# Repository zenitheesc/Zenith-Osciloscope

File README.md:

<h1 align="center" style="color:white; background-color:black">Zenith Osciloscope</h1>
<h4 align="center">This project is an educational oscilloscope based on STM32F103C8T6 aimed to be used by students on PC laboratories. The oscilloscope get some samples in a small frequency limited by the range in the STM AD converter. This samples was stored in a data pack on STM and passed by serial communication to PC. In the PC, a interface software read the serial and plot the data package</h4>

<p align="center">

</p>

---

<p align="center">

</p>
<p align = "center">
<a href="zenith.eesc@gmail.com">zenith.eesc@gmail.com</a>
</p>

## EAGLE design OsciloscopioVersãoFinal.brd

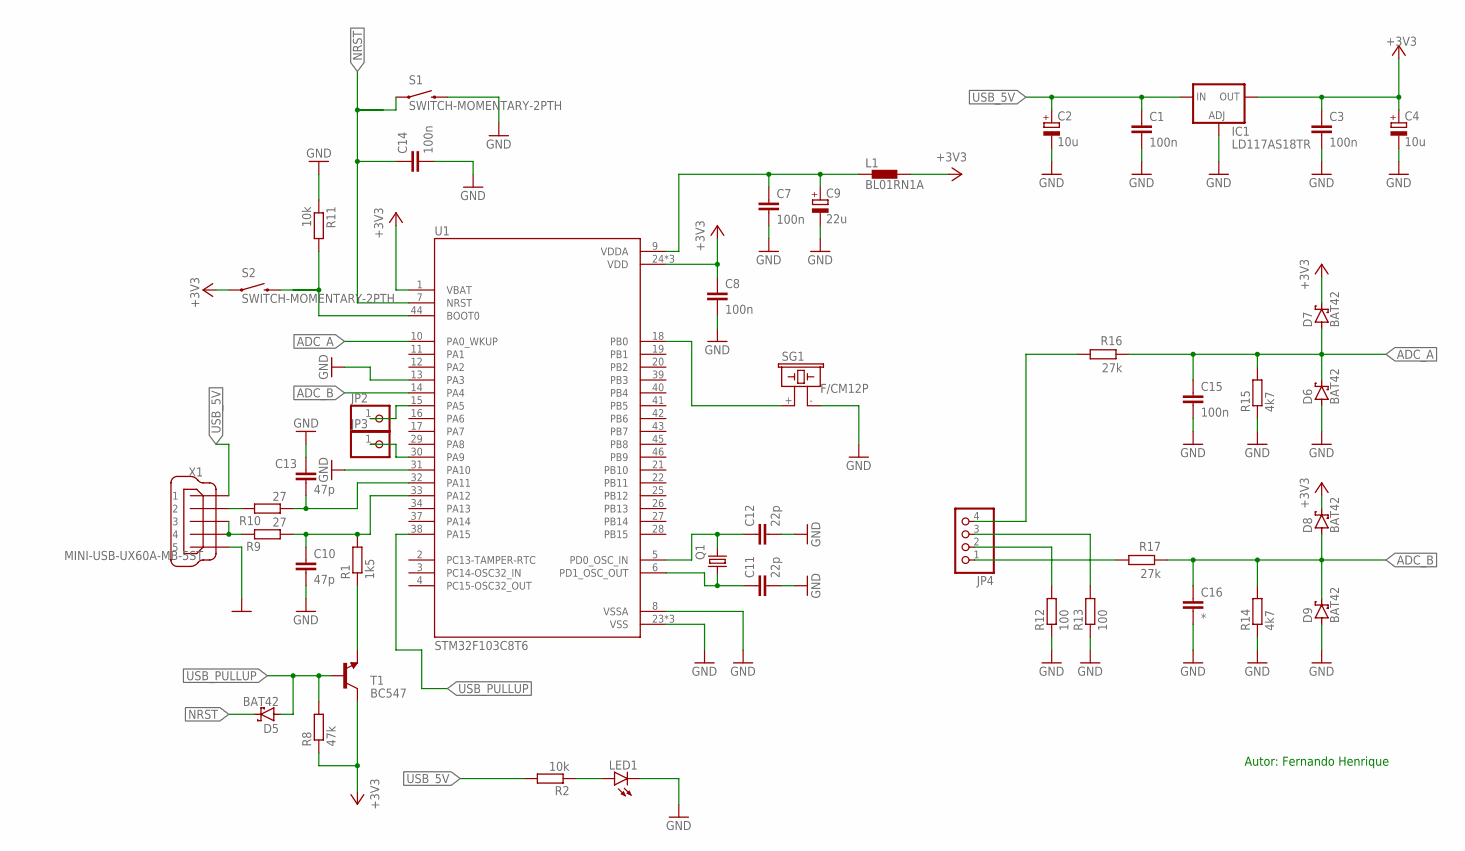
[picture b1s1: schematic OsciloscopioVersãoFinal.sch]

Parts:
C1, C3, C7, C8, C14, C15: 100n; C1206
C2, C4: 10u; B45181B
C9: 22u; B45181B
C10, C13: 47p; C1206
C11, C12: 22p; C1206
C16: *; C1206
D5, D6, D7, D8, D9: BAT42; DO35-10
IC1: LD117AS18TR; SOT223
JP2, JP3: PINHD-1X1; 1X01
JP4: PINHD-1X4; 1X04
L1: BL01RN1A
LED1: LED3MM
Q1: CRYSTALHC49U-V; HC49U-V
R1: 1k5; R1206
R2, R11: 10k; R1206
R8: 47k; R1206
R9, R10: 27; R1206
R12, R13: 100; R1206
R14, R15: 4k7; R1206
R16, R17: 27k; R1206
S1, S2: SWITCH-MOMENTARY-2PTH; TACTILE-PTH
SG1: F/CM12P
T1: BC547; TO92
U1: STM32F103C8T6; QFP50P900X900X160-48N
X1: MINI-USB-UX60A-MB-5ST; UX60A-MB-5ST

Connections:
+3V3: C3.1, C4.+, C8.1, D7.C, D8.C, IC1.4 (OUT), L1.2, R8.1, S2.1, T1.3 (C), U1.1 (VBAT), U1.24 (VDD), U1.36 (VDD), U1.48 (VDD)
ADC_A: C15.1, D6.C, D7.A, R15.2, R16.1, U1.10 (PA0_WKUP)
ADC_B: C16.1, D8.A, D9.C, R14.2, R17.1, U1.14 (PA4)
GND: C1.2, C2.-, C3.2, C4.-, C7.2, C8.2, C9.-, C10.2, C11.2, C12.2, C13.1, C14.2, C15.2, C16.2, D6.A, D9.A, IC1.1 (ADJ), LED1.K (C), R11.1, R12.1, R13.1, R14.1, R15.1, S1.3 (2), SG1.- (2), U1.8 (VSSA), U1.13 (PA3), U1.23 (VSS), U1.31 (PA10), U1.35 (VSS), U1.47 (VSS), X1.5
unnamed: LED1.A, R2.1
unnamed: SG1.+ (1), U1.18 (PB0)
unnamed: C13.2, R10.1, U1.32 (PA11)
unnamed: C10.1, R1.2, R9.1, U1.33 (PA12)
unnamed: C7.1, C9.+, L1.1, U1.9 (VDDA)
unnamed: C11.1, Q1.1, U1.6 (PD1_OSC_OUT)
unnamed: C12.1, Q1.2, U1.5 (PD0_OSC_IN)
unnamed: R1.1, T1.1 (E)
unnamed: R10.2, X1.2
unnamed: R9.2, X1.3, X1.4
unnamed: JP2.1, U1.15 (PA5)
unnamed: JP3.1, U1.30 (PA9)
unnamed: R11.2, S2.3 (2), U1.44 (BOOT0)
unnamed: JP4.1, R17.2
unnamed: JP4.2, R12.2
unnamed: JP4.3, R13.2
unnamed: JP4.4, R16.2
NRST: C14.1, D5.C, S1.1, U1.7 (NRST)
USB_5V: C1.1, C2.+, IC1.3 (IN), R2.2, X1.1
USB_PULLUP: D5.A, R8.2, T1.2 (B), U1.38 (PA15)

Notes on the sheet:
Autor: Fernando Henrique

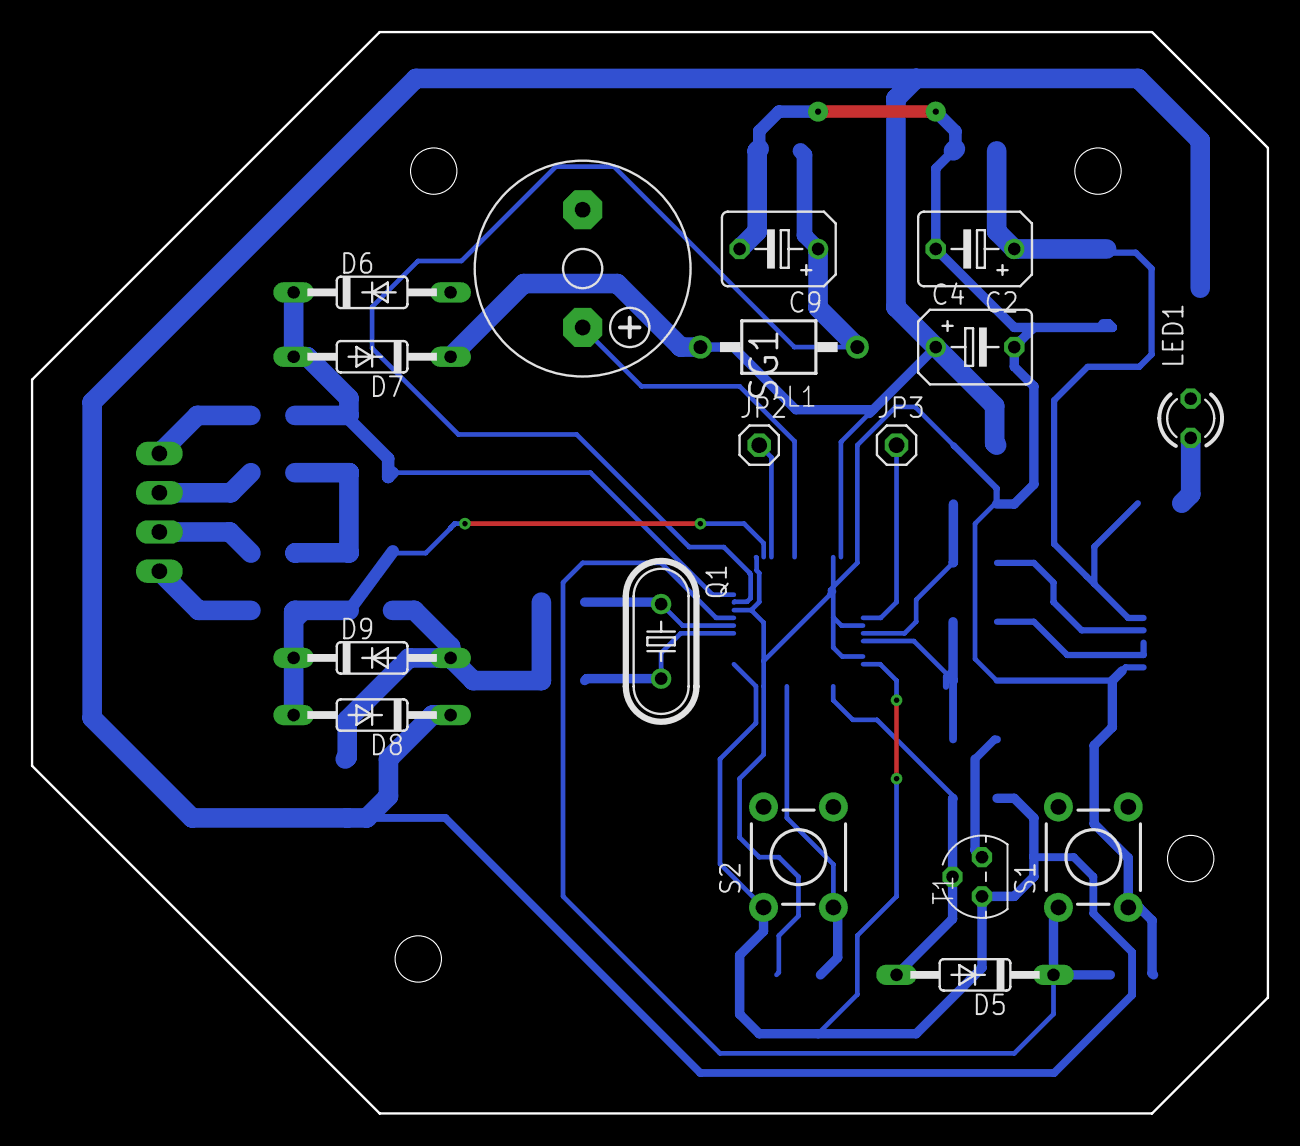
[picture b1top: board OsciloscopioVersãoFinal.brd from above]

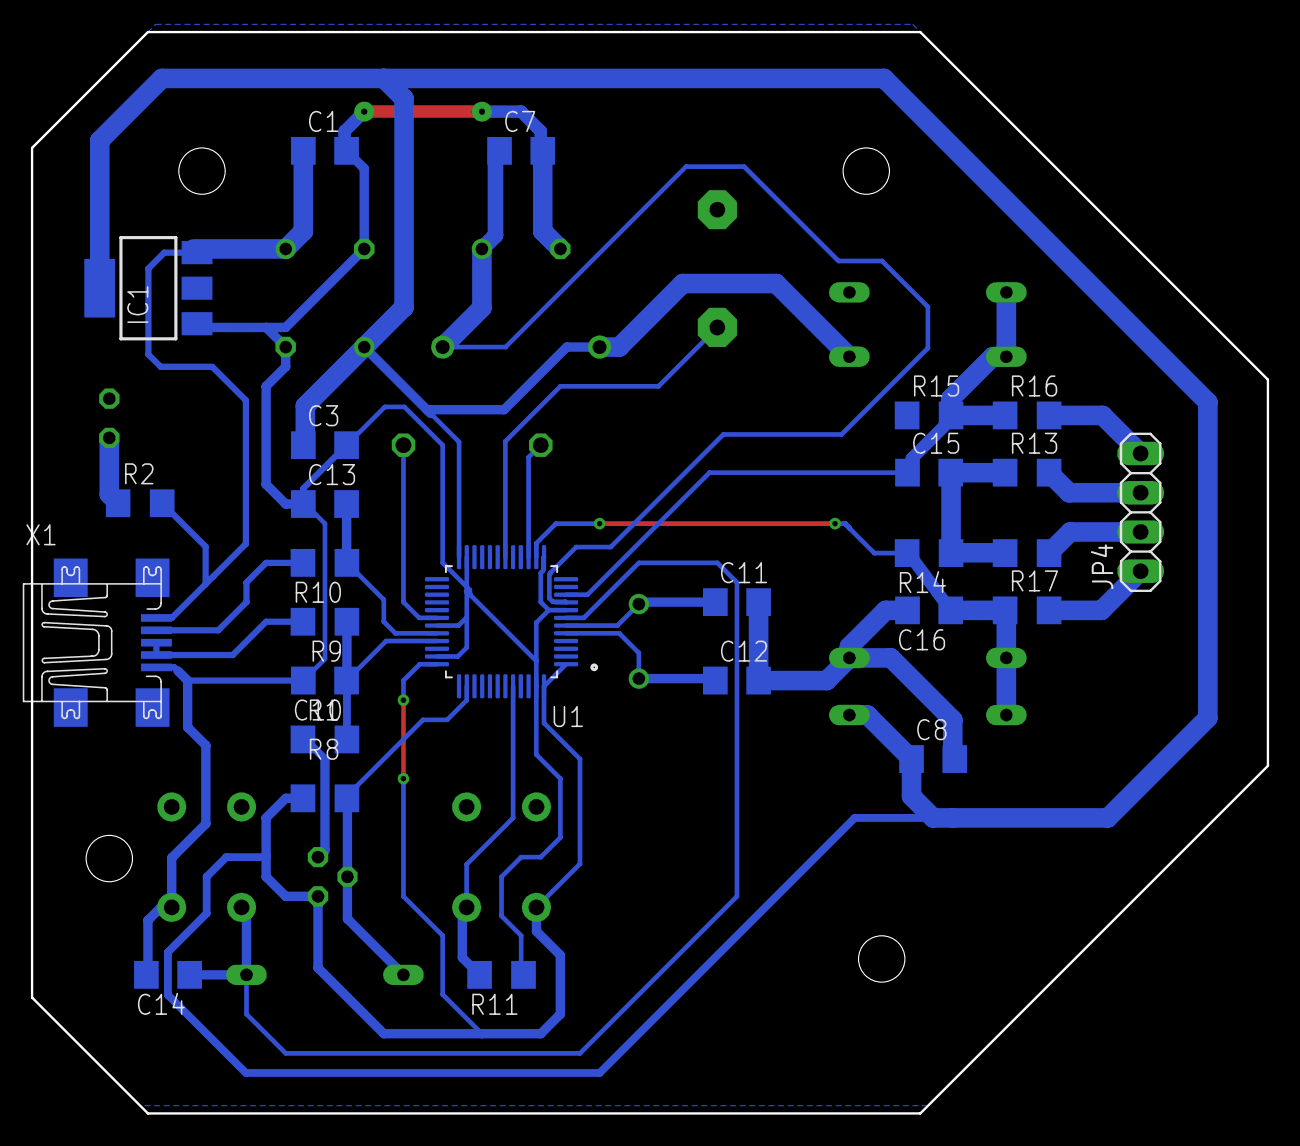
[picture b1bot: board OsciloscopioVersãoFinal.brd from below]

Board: 2 copper layers, 80.0 x 70.0 mm, 44 parts (27 on the bottom side), 24 nets.

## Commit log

2020-06-12 first
2021-02-28 💬 - File Rebuilt | Github Action Runner : 1
2021-02-28 Create LICENSE

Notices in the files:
parts and their libraries:
SparkFun-Electromechanical: Licensing: Creative Commons ShareAlike 4.0 International - https://creativecommons.org/licenses/by-sa/4.0
